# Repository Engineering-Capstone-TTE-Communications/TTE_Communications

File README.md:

# Through The Earth Communications

An engineering final year design project designed to send arbitrary data through earthy media.

[Check out the design blog!](https://sites.google.com/view/tte-boys/home) 

Or try a `python` implementation that sounds like R2D2 using your own computer! Files in `Root/Demo`. (Dirt not required).

## File structure
```
Root
└───Hardware
│   │   Gerbers,BOM
│   │   Eagle Files
└───MODEM Code
    └───MSP
        | MSP430 OOK Modem (Final Implementation)
    └───Arduino
        | Arduino NRZ MODEM
    └─── Audio - Python
        | PC FSK MODEM
```

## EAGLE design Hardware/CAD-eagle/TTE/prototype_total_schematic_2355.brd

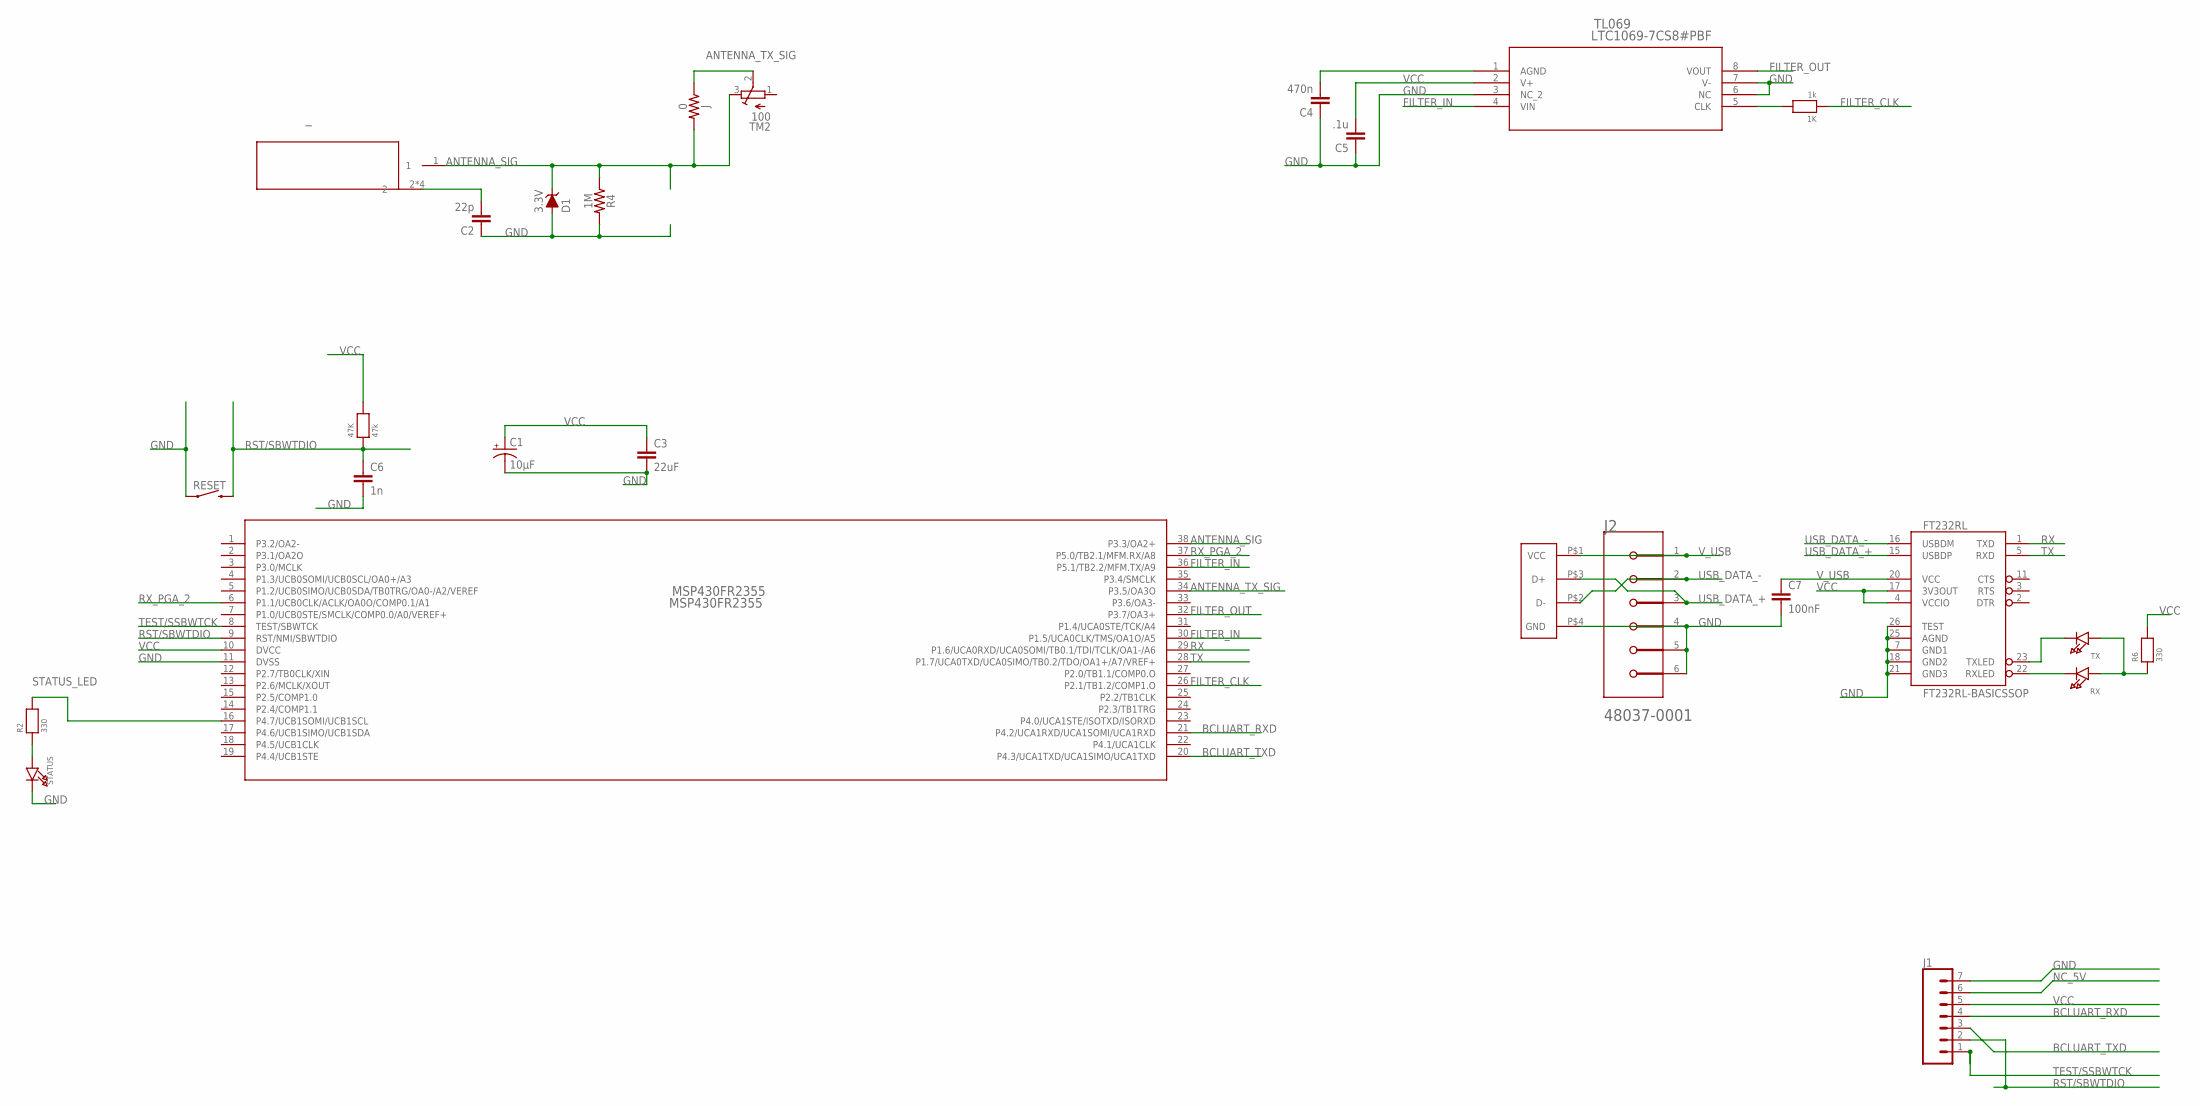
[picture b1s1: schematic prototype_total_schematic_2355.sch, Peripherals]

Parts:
1K: 1k; 0805
47K: 47k; 0805
C1: 10µF; EIA6032-NOM
C2: 22p; 0805
C3: 22uF; 0805
C4: 470n; 0805
C5: .1u; 0805
C6: 1n; 0805
C7: 100nF; 0805
D1: 3.3V; SOD-323
FT232RL: FT232RL-BASICSSOP; SSOP28DB
J: 0; 0603
J1: CONN_07NO_SILK; 1X07_NO_SILK
J2: MOLEX_48037-0001MOLEX_48037-0001_0_0; MOLEX_48037-0001_0
MSP430FR2355: MSP430FR2355; DA38
R2, R6: 330; 0805
R4: 1M; 0603
RESET: MOMENTARY-SWITCH-SPST-PTH-6.0MM; TACTILE_SWITCH_PTH_6.0MM
RX: LED0805; CHIPLED_0805
STATUS: LED0805; CHIPLED_0805
TL069: LTC1069-7CS8#PBF; SO-8_S
TM2: 100; TC33X
TX: LED0805; CHIPLED_0805
U$1: USB-PCB; PCB_USB
_: 5-1814400-1

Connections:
ANTENNA_SIG: D1.C, J.2, MSP430FR2355.38 (P3.3/OA2+), R4.1, TM2.3 (E), _.1
ANTENNA_TX_SIG: J.1, MSP430FR2355.34 (P3.5/OA3O), TM2.2 (S)
BCLUART_RXD: J1.4, MSP430FR2355.21 (P4.2/UCA1RXD/UCA1SOMI/UCA1RXD)
BCLUART_TXD: J1.3, MSP430FR2355.20 (P4.3/UCA1TXD/UCA1SIMO/UCA1TXD)
FILTER_CLK: 1K.1, MSP430FR2355.26 (P2.1/TB1.2/COMP1.O)
FILTER_IN: MSP430FR2355.30 (P1.5/UCA0CLK/TMS/OA1O/A5), MSP430FR2355.36 (P5.1/TB2.2/MFM.TX/A9), TL069.4 (VIN)
FILTER_OUT: MSP430FR2355.32 (P3.7/OA3+), TL069.8 (VOUT)
GND: C1.C (-), C2.1, C3.2, C4.1, C5.1, C6.2, C7.2, D1.A, FT232RL.7 (GND1), FT232RL.18 (GND2), FT232RL.21 (GND3), FT232RL.25 (AGND), FT232RL.26 (TEST), J1.7, J2.4, J2.5 (MNT_1), J2.6 (MNT_2), MSP430FR2355.11 (DVSS), R4.2, RESET.1, STATUS.C, TL069.3 (NC_2), TL069.6 (NC), TL069.7 (V-), U$1.P$4 (GND)
unnamed: 1K.2, TL069.5 (CLK)
unnamed: C2.2, _.2, _.3 (2), _.4 (2), _.5 (2)
unnamed: C4.2, TL069.1 (AGND)
unnamed: R2.1, STATUS.A
unnamed: FT232RL.22 (RXLED), RX.C
unnamed: FT232RL.23 (TXLED), TX.C
unnamed: R6.1, RX.A, TX.A
NC_5V: J1.6
P1.3/UCB0SOMI/UCB0SCL/OA0+/A3: MSP430FR2355.4 (P1.3/UCB0SOMI/UCB0SCL/OA0+/A3)
P3.0/MCLK: MSP430FR2355.3 (P3.0/MCLK)
P3.6/OA3-: MSP430FR2355.33 (P3.6/OA3-)
RST/SBWTDIO: 47K.1, C6.1, J1.2, MSP430FR2355.9 (RST/NMI/SBWTDIO), RESET.3 (2)
RX: FT232RL.1 (TXD), MSP430FR2355.29 (P1.6/UCA0RXD/UCA0SOMI/TB0.1/TDI/TCLK/OA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)
RX_PGA_2: MSP430FR2355.6 (P1.1/UCB0CLK/ACLK/OA0O/COMP0.1/A1), MSP430FR2355.37 (P5.0/TB2.1/MFM.RX/A8)
STATUS_LED: MSP430FR2355.16 (P4.7/UCB1SOMI/UCB1SCL), R2.2
TEST/SSBWTCK: J1.1, MSP430FR2355.8 (TEST/SBWTCK)
TX: FT232RL.5 (RXD), MSP430FR2355.28 (P1.7/UCA0TXD/UCA0SIMO/TB0.2/TDO/OA1+/A7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)
USB_DATA_+: FT232RL.15 (USBDP), J2.3, U$1.P$3 (D+)
USB_DATA_-: FT232RL.16 (USBDM), J2.2, U$1.P$2 (D-)
VCC: 47K.2, C1.A (+), C3.1, C5.2, FT232RL.4 (VCCIO), FT232RL.17 (3V3OUT), J1.5, MSP430FR2355.10 (DVCC), R6.2, TL069.2 (V+)
V_USB: C7.1, FT232RL.20 (VCC), J2.1, U$1.P$1 (VCC)

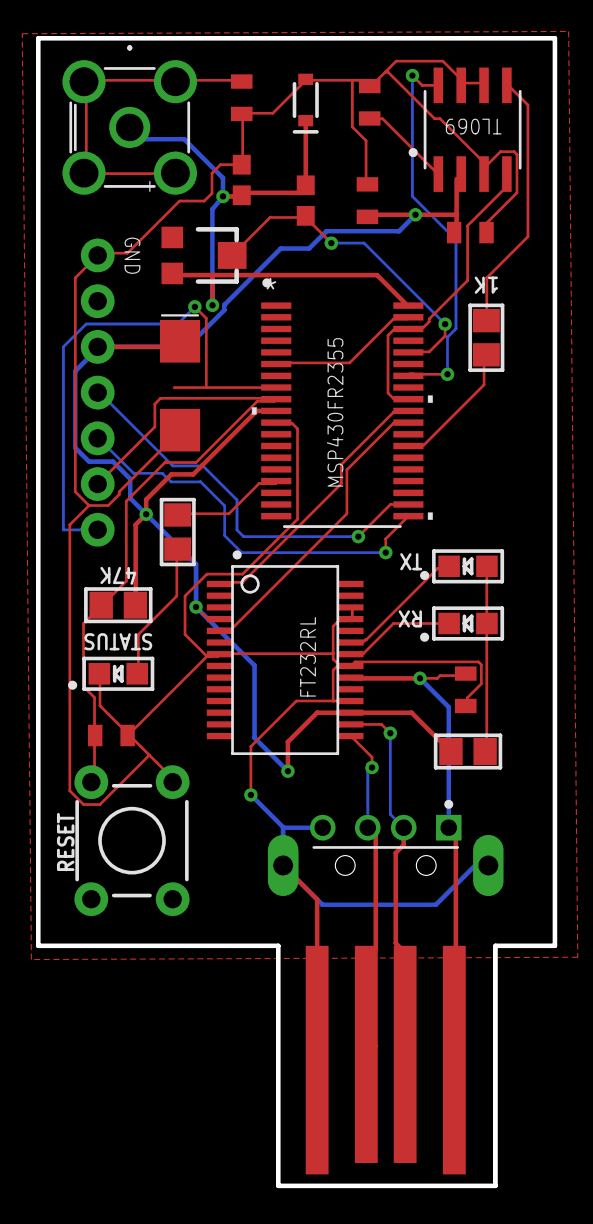
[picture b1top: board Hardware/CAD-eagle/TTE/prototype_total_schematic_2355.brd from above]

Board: 2 copper layers, 28.7 x 63.8 mm, 26 parts (0 on the bottom side), 25 nets.

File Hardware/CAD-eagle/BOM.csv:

Qty,Value,Device,Package,Parts,Description,CENTROID_NOT_SPECIFIED,DATASHEET,DESCRIPTION,DIGI-KEY_PART_NUMBER,DIGI-KEY_PURCHASE_URL,DIGIKEY_DESCRIPTION,DIGIKEY_PART_NUMBER,IMPORTED_FROM,IS_FEMALE,LEAD_FREE,MANUFACTURER_PART_NUMBER,MF,MOUSER_PART_NUMBER,MP,MPN,NUM_PINS,OCTOPART_PART_NUMBER,PACKAGE,PREFIX,PROD_ID,ROHS,SF_SKU,TEMPERATURE_RANGE_HIGH,TEMPERATURE_RANGE_LOW,VALUE,VENDOR
3,,LED0805,CHIPLED_0805,RX,,,,,,,,,,,,,,,,,,,,,,,,,,,
1,,MOMENTARY-SWITCH-SPST-PTH-6.0MM,TACTILE_SWITCH_PTH_6.0MM,RST,Momentary Switch (Pushbutton) - SPST,,,,,,,,,,,,,,,,,,,, SWCH-08441,,COM-00097,,,,
1,100,TRIMPOTTC33X,TC33X,TM2,SMT trimmer potentiometer part number TC33X,,,,,,,,,,,,,,,,,,,,,,,,,,
1,100n,22UF-0805-6.3V-20%,805,C5,22µF ceramic capacitors,,,,,,,,,,,,,,,,,,,,CAP-08402,,,,,22uF,
1,100nF,22UF-0805-6.3V-20%,805,C2,22µF ceramic capacitors,,,,,,,,,,,,,,,,,,,,CAP-08402,,,,,22uF,
1,10µF,10UF-POLAR-EIA6032-25V-10%,EIA6032-NOM,C1,10.0µF polarized capacitors,,,,,,,,,,,,,,,,,,,,CAP-12984,,,,,10µF,
1,1M,2.0KOHM-0603-1/10W-5%,603,R4,2kΩ resistor,,,,,,,,,,,,,,,,,,,,RES-08296,,,,,2.0k,
1,1k,RESISTOR0805,805,1K,Resistors,,,,,,,,,,,,,,,,,,,,,,,,,,
1,1n,22UF-0805-6.3V-20%,805,C6,22µF ceramic capacitors,,,,,,,,,,,,,,,,,,,,CAP-08402,,,,,22uF,
1,22uF,22UF-0805-6.3V-20%,805,C3,22µF ceramic capacitors,,,,,,,,,,,,,,,,,,,,CAP-08402,,,,,22uF,
1,3.3V,DIODE-ZENER-MM3Z3V3T1G,SOD-323,D1,Zener Diode,,,,,,,,,,,,,,,,,,,,DIO-11284,,,,,3.3V,
2,330,RESISTOR0805,805,R2,,,,,,,,,,,,,,,,,,,,,,,,,,,
6,455-1750-1-ND,CONN_04,1X04,GND,,,,,,,,,,,,,,,,,,,,,,,,,,,
1,470n,22UF-0805-6.3V-20%,805,C4,22µF ceramic capacitors,,,,,,,,,,,,,,,,,,,,CAP-08402,,,,,22uF,
1,47k,RESISTOR0805,805,47K,Resistors,,,,,,,,,,,,,,,,,,,,,,,,,,
1,5-1814400-1,5-1814400-1,5-1814400-1,RIGHT_ANGLE_SMA_MALE,,,,,,,,,,,,518144001,,,,,,,,,,,,,,,TE Connectivity
1,FILT,CONN_02,1X02,FILT,Multi connection point. Often used as Generic Header-pin footprint for 0.1 inch spaced/style header connections,,,,,,,,,,,,,,,,,,,,,,,,,,
1,FT232RL-BASICSSOP,FT232RL-BASICSSOP,SSOP28DB,FT232RL,USB UART,,,,,,,,,,,,,,,,,,,,,,,,,,
1,LTC1069-7CS8#PBF,LTC1069-7CS8#PBF,SO-8_S,TL069,,,, LTC1069-7 - Linear Phase 8th Order Lowpass Filter ,LTC1069-7CS8#PBF-ND,https://www.digikey.com/product-detail/en/linear-technology-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,,,,,,,Linear Technology,,LTC1069-7CS8#PBF,,,,SOIC-8 Linear Technology,,,,,,,,
1,MOLEX_48037-0001MOLEX_48037-0001_0_0,MOLEX_48037-0001MOLEX_48037-0001_0_0,MOLEX_48037-0001_0,J2,Universal Serial Bus (USB) Shielded I/O Plug,,,,,,,,,,,,,,,,,,,,,,,,,,
1,MSP430FR2355,MSP430FR2355,DA38,MSP430,,,,,,,,,,,,,,,,,,,,,,,,,,,
2,RX,CONN_02,1X02,J4,,,,,,,,,,,,,,,,,,,,,,,,,,,

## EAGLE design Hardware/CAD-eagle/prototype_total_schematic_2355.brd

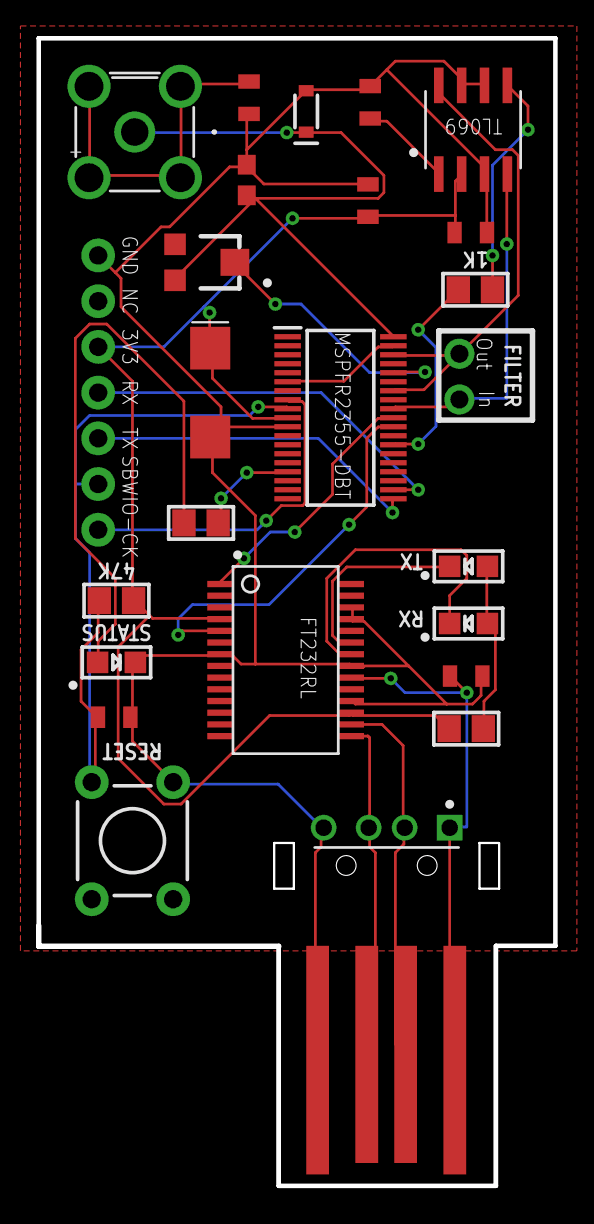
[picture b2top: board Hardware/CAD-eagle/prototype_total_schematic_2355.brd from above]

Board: 2 copper layers, 28.7 x 63.7 mm, 26 parts (0 on the bottom side), 25 nets.

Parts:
1K: 1k; 0805
47K: 47k; 0805
C1: 10u; EIA6032-NOM
C2: 22p; 0805
C3: 22u; 0805
C4: 470n; 0805
C5: .1u; 0805
C6: 1n; 0805
C7: 100n; 0805
D1: 3.3V; SOD-323
FILTER: 1X02_ROUND
FT232RL: FT232RL-BASICSSOP; SSOP28DB
J1: 1X07_NO_SILK
J2: MOLEX_48037-0001MOLEX_48037-0001_0_0; MOLEX_48037-0001_0
MSPFR2355-DBT: MSPFR2355-DBT; SOP50P640X120-38N
R2, R6: 330; 0805
R4: 1M; 0603
RESET: TACTILE_SWITCH_PTH_6.0MM
RX: CHIPLED_0805
STATUS: CHIPLED_0805
TL069: LTC1069-7CS8#PBF; SO-8_S
TM2: 100; TC33X
TX: CHIPLED_0805
U$1: USB-PCB; PCB_USB
_: 5-1814400-1

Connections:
ANTENNA_SIG: D1.C, MSPFR2355-DBT.38, R4.1, TM2.3, _.1
ANTENNA_TX_SIG: MSPFR2355-DBT.34, TM2.2
BCLUART_RXD: J1.4, MSPFR2355-DBT.21
BCLUART_TXD: J1.3, MSPFR2355-DBT.20
FILTER_CLK: 1K.1, MSPFR2355-DBT.26
FILTER_IN: FILTER.2, MSPFR2355-DBT.30, TL069.4
FILTER_OUT: FILTER.1, MSPFR2355-DBT.32, MSPFR2355-DBT.36, TL069.8
GND: C1.C, C2.1, C3.2, C4.1, C5.1, C6.2, C7.2, D1.A, FT232RL.7, FT232RL.18, FT232RL.21, FT232RL.25, FT232RL.26, J1.7, J2.4, MSPFR2355-DBT.11, R4.2, RESET.1, STATUS.C, TL069.3, TL069.6, TL069.7, U$1.P$4
unnamed: 1K.2, TL069.5
unnamed: C2.2, _.2, _.3, _.4, _.5
unnamed: C4.2, TL069.1
unnamed: R2.1, STATUS.A
unnamed: FT232RL.22, RX.C
unnamed: FT232RL.23, TX.C
unnamed: R6.1, RX.A, TX.A
RST/SBWTDIO: 47K.1, C6.1, J1.2, MSPFR2355-DBT.9, RESET.3
RX: FT232RL.1, MSPFR2355-DBT.29
RX_PGA_2: MSPFR2355-DBT.6, MSPFR2355-DBT.37
STATUS_LED: MSPFR2355-DBT.16, R2.2
TEST/SSBWTCK: J1.1, MSPFR2355-DBT.8
TX: FT232RL.5, MSPFR2355-DBT.28
USB_DATA_+: FT232RL.15, J2.3, U$1.P$3
USB_DATA_-: FT232RL.16, J2.2, U$1.P$2
VCC: 47K.2, C1.A, C3.1, C5.2, FT232RL.4, FT232RL.17, J1.5, MSPFR2355-DBT.10, R6.2, TL069.2
V_USB: C7.1, FT232RL.20, J2.1, U$1.P$1

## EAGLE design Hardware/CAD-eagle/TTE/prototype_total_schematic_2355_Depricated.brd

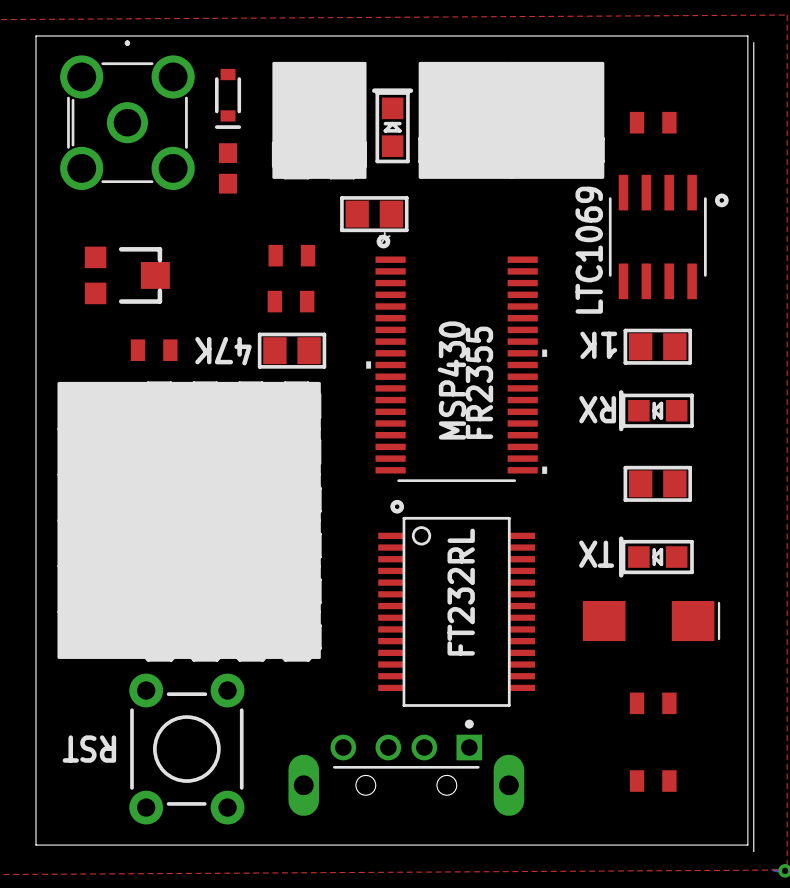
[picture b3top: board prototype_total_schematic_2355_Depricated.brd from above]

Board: 2 copper layers, 39.9 x 45.3 mm, 32 parts (0 on the bottom side), 35 nets.

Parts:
1K: 1k; 0805
47K: 47k; 0805
C1: 10µF; EIA6032-NOM
C2: 100nF; 0805
C3: 22uF; 0805
C4: 470n; 0805
C5: .1u; 0805
C6: 1n; 0805
C7: 22p; 0805
D1: 3.3V; SOD-323
FILT: FILT; 1X02
FT232RL: FT232RL-BASICSSOP; SSOP28DB
GND: 455-1750-1-ND; 1X04
J2: MOLEX_48037-0001MOLEX_48037-0001_0_0; MOLEX_48037-0001_0
J4: RX; 1X02
MSP430: MSP430FR2355; DA38
R2, R6: 330; 0805
R4: 1M; 0603
RIGHT_ANGLE_SMA_MALE: 5-1814400-1
RST: TACTILE_SWITCH_PTH_6.0MM
RX: CHIPLED_0805
RXD: 455-1750-1-ND; 1X04
SIG: RX; 1X02
STATUS: CHIPLED_0805
TCK: 455-1750-1-ND; 1X04
TDIO: 455-1750-1-ND; 1X04
TL069: LTC1069-7CS8#PBF; SO-8_S
TM2: 100; TC33X
TX: CHIPLED_0805
TXD: 455-1750-1-ND; 1X04
VCC: 455-1750-1-ND; 1X04

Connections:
ADC: J4.2, MSP430.5, MSP430.6
ANTENNA_SIG: D1.C, MSP430.38, R4.1, RIGHT_ANGLE_SMA_MALE.1, SIG.1, TM2.1
ANTENNA_TX_SIG: C7.1, MSP430.34, SIG.2
BCLUART_RXD: MSP430.21, MSP430.29, RXD.2
BCLUART_RXD_EXT: RXD.3, RXD.4
BCLUART_RXD_USB: FT232RL.1, RXD.1
BCLUART_TXD: MSP430.20, MSP430.28, TXD.2
BCLUART_TXD_EXT: TXD.3, TXD.4
BCLUART_TXD_USB: FT232RL.5, TXD.1
FILTER_CLK: 1K.1, MSP430.26
FILTER_IN: FILT.2, MSP430.30, MSP430.37, TL069.4
FILTER_OUT: FILT.1, MSP430.32, TL069.8
GND: C1.C, C2.2, C3.2, C4.1, C5.1, C6.2, D1.A, FT232RL.7, FT232RL.18, FT232RL.21, FT232RL.25, FT232RL.26, GND.2, J2.4, J2.5, J2.6, MSP430.11, R4.2, RIGHT_ANGLE_SMA_MALE.2, RIGHT_ANGLE_SMA_MALE.3, RIGHT_ANGLE_SMA_MALE.4, RIGHT_ANGLE_SMA_MALE.5, RST.1, STATUS.C, TL069.3, TL069.6, TL069.7
GND_EXT: GND.3, GND.4
unnamed: 1K.2, TL069.5
unnamed: C7.2, TM2.2
unnamed: C4.2, TL069.1
unnamed: R2.1, STATUS.A
unnamed: FT232RL.22, RX.C
unnamed: FT232RL.23, TX.C
unnamed: R6.1, RX.A, TX.A
RST/SBWTDIO: 47K.1, C6.1, MSP430.9, RST.3, TDIO.2
RST/SBWTDIO_EXT: TDIO.3, TDIO.4
RST/SBWTDIO_USB: FT232RL.2, TDIO.1
RX_PGA_1: J4.1, MSP430.2, MSP430.4
STATUS_LED: MSP430.15, R2.2
TEST/SSBWTCK: MSP430.8, TCK.2
TEST/SSBWTCK_USB: FT232RL.3, TCK.1
TST/SBWTCK_EXT: TCK.3, TCK.4
USB_DATA_+: FT232RL.15, J2.2
USB_DATA_-: FT232RL.16, J2.3
VCC: 47K.2, C1.A, C2.1, C3.1, C5.2, MSP430.10, R6.2, TL069.2, VCC.2
VCC_EXT: VCC.3, VCC.4
VCC_USB: FT232RL.4, FT232RL.17, VCC.1
V_USB: FT232RL.20, J2.1

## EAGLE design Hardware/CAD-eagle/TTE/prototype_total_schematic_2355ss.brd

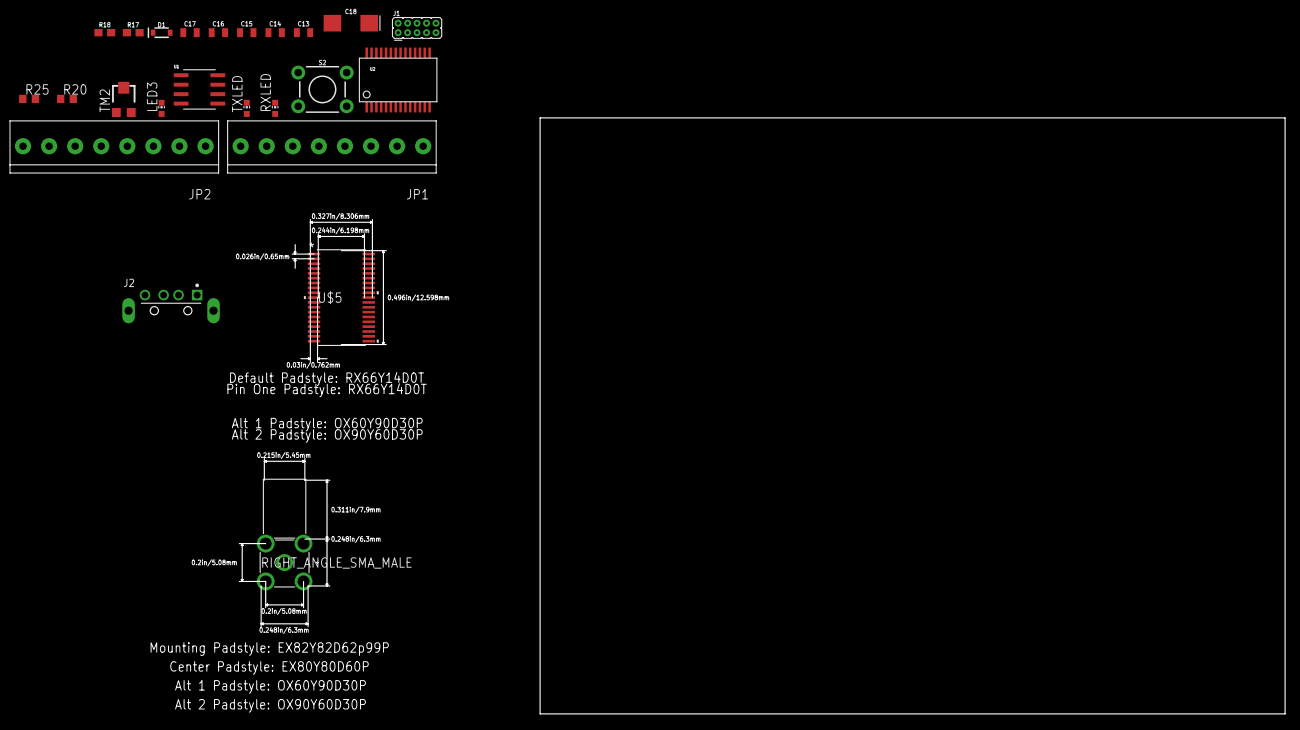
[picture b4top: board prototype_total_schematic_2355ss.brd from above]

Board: 2 copper layers, 152.4 x 80.0 mm, 24 parts (0 on the bottom side), 26 nets, no tracks yet.

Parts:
C13: 100nF; 0805
C14: 22uF; 0805
C15: 470n; 0805
C16: 100n; 0805
C17: 1000p; 0805
C18: 10µF; EIA6032-NOM
D1: 3.3V; SOD-323
J1: 2X5_PTH_SILK_.05
J2: MOLEX_48037-0001MOLEX_48037-0001_0_0; MOLEX_48037-0001_0
JP1, JP2: 1X08-3.5MM
LED3: CHIP-LED0603
R17: 1k; 0603
R18: 47k; 0603
R20, R25: 330; R0603
RIGHT_ANGLE_SMA_MALE: 5-1814400-1
RXLED: CHIP-LED0603
S2: TACTILE_SWITCH_PTH_6.0MM
TM2: TC33X
TXLED: CHIP-LED0603
U1: LTC1069-7CS8#PBF; SO-8_S
U2: FT232RL-BASICSSOP; SSOP28DB
U$5: MSP430FR2355; DA38

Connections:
!RTS!_JTAG_TCK: J1.7, U2.3, U$5.8
ADC: U$5.5, U$5.6
ANTENNA_SIG: D1.C, JP1.8, JP2.8, RIGHT_ANGLE_SMA_MALE.1, TM2.1, U$5.38
ANTENNA_TX_SIG: TM2.2, U$5.34
FILTER_CLK: R17.1, U$5.26
FILTER_IN: JP1.6, JP2.6, U1.4, U$5.30
FILTER_OUT: JP1.7, JP2.7, U1.8, U$5.32
GND: C13.2, C14.2, C15.1, C16.1, C17.2, C18.C, D1.A, J1.3, J1.5, J1.9, J2.4, J2.5, J2.6, JP1.2, JP2.2, LED3.C, S2.1, U1.3, U1.6, U1.7, U2.7, U2.18, U2.21, U2.25, U2.26, U$5.11
JTAG_TCK: J1.4, U$5.31
unnamed: R17.2, U1.5
unnamed: C15.2, U1.1
unnamed: LED3.A, R20.1
unnamed: RXLED.C, U2.22
unnamed: TXLED.C, U2.23
unnamed: R25.1, RXLED.A, TXLED.A
RESET_JTAG_RESET: C17.1, J1.10, R18.1, S2.3, U2.2, U$5.9
RX_INPUT_DAC_JTAG_TMS: J1.2, JP1.5, JP2.5
RX_PGA_1: U$5.2, U$5.4
STATUS_LED: R20.2, U$5.15
UART_BSL_RX_JTAG_DIN: J1.8, JP1.3, JP2.3, U2.1, U$5.21, U$5.29
UART_BSL_TX_JTAG_DOUT: J1.6, JP1.4, JP2.4, U2.5, U$5.20, U$5.28
USB_DATA_+: J2.2, U2.15
USB_DATA_-: J2.3, U2.16
VCC: C13.1, C14.1, C16.2, C18.A, J1.1, R18.2, R25.2, U1.2, U$5.10
VCC_3V3: U2.4, U2.17
V_USB: J2.1, JP1.1, JP2.1, U2.20

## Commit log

2018-11-03 MatLab Files for various common (and not so common) encoding schemes.
2018-11-14 Barker Sequence Generator, (note: L<=13)
2018-12-23 Simulations, Implementations, and Imagination(s)
2019-01-02 Restructure and add local relevant files
2019-01-07 Adding a novel approach to a github tutorial
2019-01-07 Rename notes_on_git.md to README.md
2019-01-26 Adding GUI Progress, Audio-BFSK reciever
2019-01-29 Successful audio BFSK MODEM
2019-01-30 M-FSK working
2019-01-30 Optimizing Byte Rate
2019-02-10 Working ADC code, for reference.
2019-02-10 review
2019-02-10 Working adc-dac connection
2019-02-10 Including circuit schematic
2019-02-14 Script for demonstrations, test code for demonstrations
2019-02-19 Rename script.md to README.md
2019-02-20 Including initial hardware design files
2019-02-26 Latest hardware revisions
2019-02-27 Nightly Update
2019-02-28 Nightly build. Hopefully final version.
2019-03-03 MSP430 Initial Code, Serial Port Echo Code
2019-03-03 Serial Port Example
2019-03-03 Adding microcontroller TI documentation
2019-03-05 Submitted orderss. finally. :)
2019-03-07 PGA Stage 2 Working
2019-03-07 Cascaded RX PGA array confirmed
2019-03-08 Reciever Pipeline Confirmed, Updated Gerbers, included tx coupling capacitor for rx offset
2019-03-12 MODEM Files
2019-03-12 Working PWM TB2.2
2019-03-13 User-friendly USB interface code
2019-03-13 User friendly USB & FIFO libraries
2019-03-14 Filter Clock Practical Usage Verification
2019-03-14 PWM DAC Confirmed. 3v3 Logic Filter Confirmed -> need to decouple agnd
2019-03-15 Phy Baud Simulator
2019-03-15 Save point for video router
2019-03-15 Switched to a class structure
2019-03-17 AFE Online, PGA Tuning offline
2019-03-17 Life is hard
2019-03-18 Working USB -> DAC
2019-03-18 Beep boop preamble bot
2019-03-18 Sine generator online
2019-03-18 Communication is so hard
2019-03-22 cooler dac
2019-03-22 cooler adc
2019-03-23 Pre-Integration C Checkpoint
2019-03-23 USB Verification
2019-03-24 Re-did mod/demod unfortunately
2019-03-24 Code Integration Checkpoint
2019-03-24 Software integration success\!
2019-03-24 USB integration success\!
2019-03-24 8 MHz clk online
2019-03-24 8MHz clk, 19200 baud serial
2019-03-24 Stats hook
2019-03-25 Soil test worthy :)
2019-03-25 approx 1 in 3800 error rate 0 SNR
2019-03-25 SNR Display
2019-03-25 Re-integrating filter
2019-03-25 Rework TX/RX pipeline
2019-03-25 heckpoint
2019-04-15 V3 PCB schematics Ordered
2019-04-21 50kHz sampline, adc dac sync
2019-04-21 0%BER at no SNR
2019-04-22 tough life
2019-04-24 Presentable Master Branch
2019-04-24 Removing Needless Files
2019-06-28 Final Commit :C

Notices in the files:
parts and their libraries:
SparkFun-Resistors: Licensing: Creative Commons ShareAlike 4.0 International - https://creativecommons.org/licenses/by-sa/4.0
microbuilder: This work is placed in the public domain, and may be freely used for commercial and non-commercial work with the following conditions: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
